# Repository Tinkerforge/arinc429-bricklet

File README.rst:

ARINC429 Bricklet
=================

**This Bricklet is currently in development.**

This repository contains the firmware source code and the hardware design
files. The documentation generator configs can be found at
https://github.com/Tinkerforge/generators

Repository Content
------------------

software/:
 * examples/: Examples for all supported languages
 * build/: Compiled files
 * src/: Source code of firmware
 * Makefile: Makefile to build project

hardware/:
 * Contains KiCad project files and additionally schematics as PDF

datasheets/:
 * Contains datasheets for sensors and complex ICs that are used

Hardware
--------

The hardware is designed with the open source EDA Suite KiCad
(http://www.kicad.org). Before you are able to open the files,
you have to install the Tinkerforge kicad-libraries
(https://github.com/Tinkerforge/kicad-libraries). You can either clone
them directly in hardware/ or clone them in a separate folder and
symlink them into hardware/
(ln -s kicad_path/kicad-libraries project_path/hardware). After that you
can open the .pro file in hardware/ with KiCad and from there view and
modify the schematics and the PCB layout.

Software
--------

If you want to do your own Brick/Bricklet firmware development we highly
recommend that you use our build environment setup script and read the
tutorial (https://www.tinkerforge.com/en/doc/Tutorials/Tutorial_Build_Environment/Tutorial.html).

To compile the C code we recommend you to install the newest GNU Arm Embedded
Toolchain (https://launchpad.net/gcc-arm-embedded/+download).
You also need to install bricklib2 (https://github.com/Tinkerforge/bricklib2).

You can either clone it directly in software/src/ or clone it in a
separate folder and symlink it into software/src/
(ln -s bricklib_path/bricklib2 project_path/software/src/). Finally make sure to
have CMake installed (http://www.cmake.org/cmake/resources/software.html).

After that you can build the firmware by invoking make in software/.
The firmware (.zbin) can then be found in software/build/ and uploaded
with brickv (click button "Flashing" on start screen).

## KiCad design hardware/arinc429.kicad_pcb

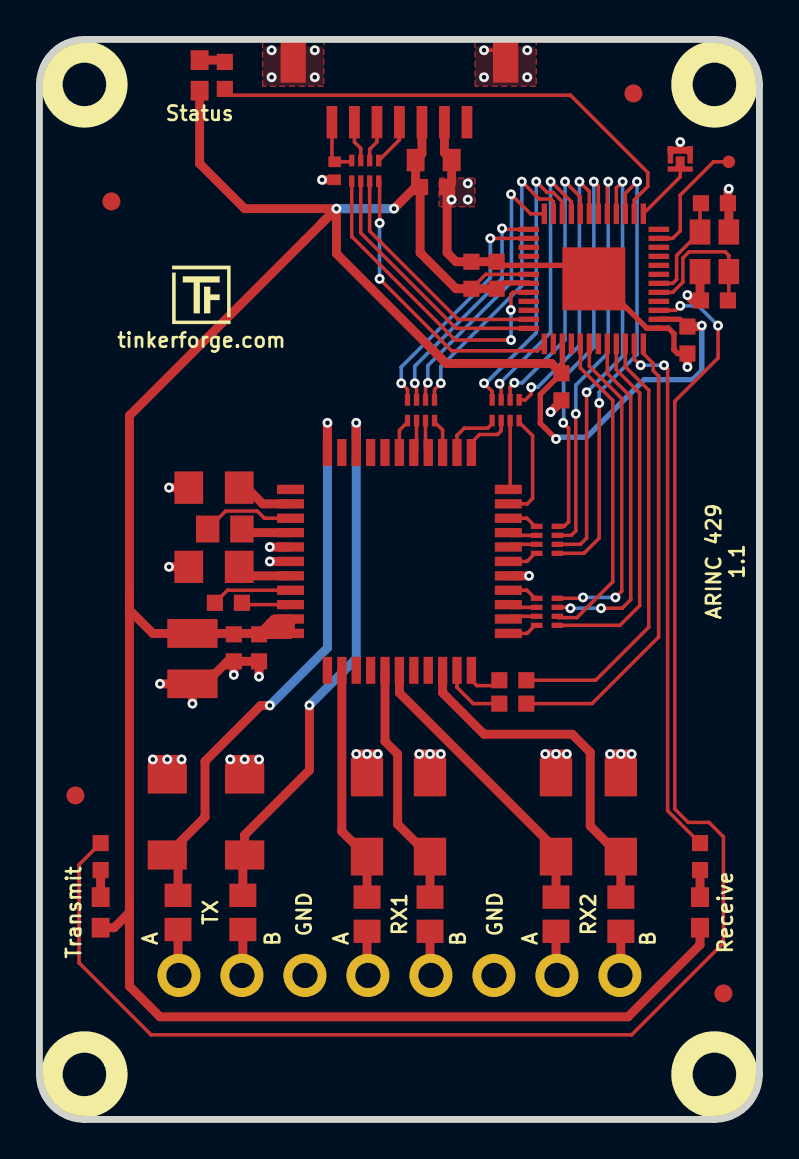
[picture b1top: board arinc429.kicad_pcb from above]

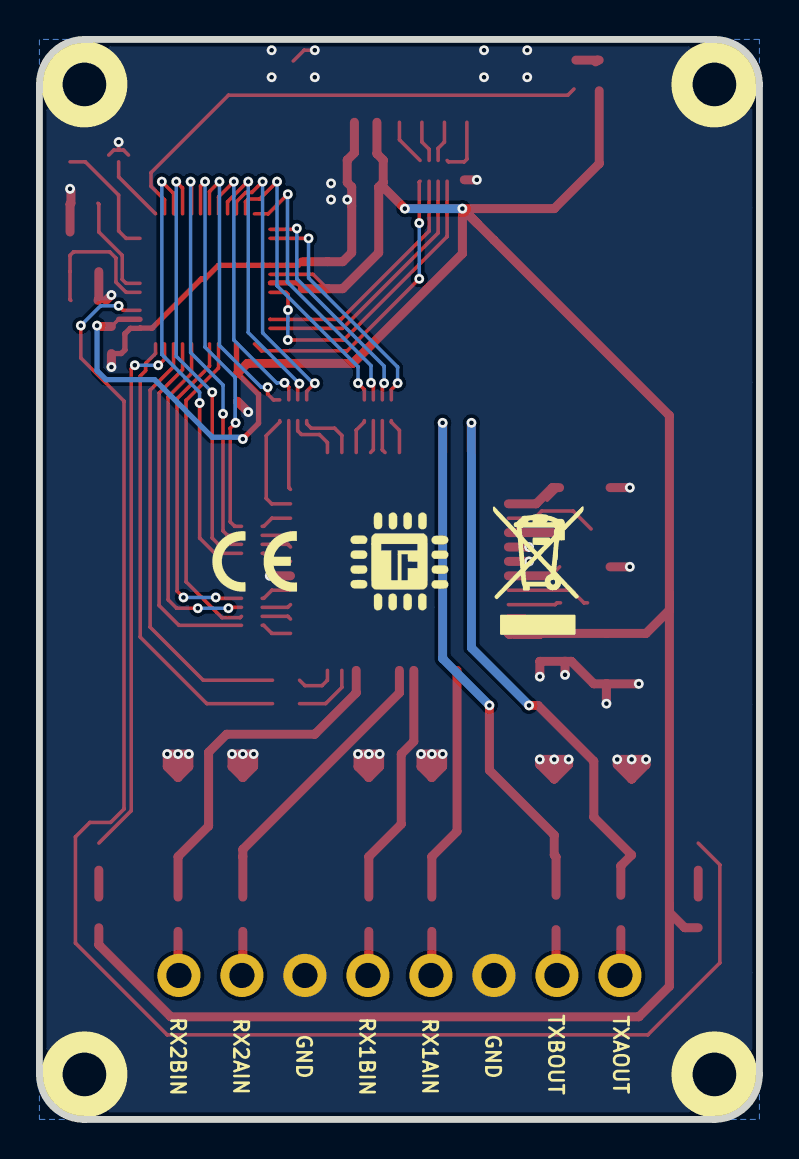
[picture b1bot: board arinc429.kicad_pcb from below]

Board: 2 copper layers, 40.0 x 60.0 mm, 58 parts (2 on the bottom side), 74 nets.

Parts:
C1: 10uF; C0805
C2: 1uF; C0603F
C3, C4, C5, C12: 100nF; C0603F
C6: 220nF; C0603F
C7: 220pF; C0402F
C8, C9: 10pF; C0603F
C10: 47uF; 3528-21
C11: 10nF; C0603F
C13, C15: 47uF/10V; C1206E
C14: 2,2uF/16V; 0805E
C16: 470nF/16V; 0603F
D1, D2: SMBJ-6.5CA; SMB
D3, D8, D9: blue; D0603E
D4, D5, D6, D7: SMAJ-6.5CA; DO-214AC
Fiducial_Mark: VAL**; Fiducial_Mark
Fiducial_Mark#2, Fiducial_Mark#3, Fiducial_Mark#4: VAL**; Fiducial_Mark
P1: CON-SENSOR2
P2: BOOT; SolderJumper
P3: DEBUG; DEBUG_PAD
P4: IND 8Pol; OQ_8P
R1, R10, R11: 1k; R0603F
R2, R3: 100; R0603F
R4, R5, R6, R7: 40,2k; R0805E
R8, R9: 31,6; R0805E
RP1: 82; 4X0402
RP2, RP3, RP4, RP5: 100; 4X0402
U1: XMC1404; QFN48-EP2
U2, U3, U4, U5: DRILL; DRILL_NP
U6: HI-3593PQIF; PQFP-44_10x10mm
VAL: WEEE_7mm
VAL#2: CE_5mm
X1: 16MHz; CRYSTAL_3225

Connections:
CLOCK: R3.2, U1.34
GND: C1.1, C2.1, C3.2, C4.2, C5.2, C6.2, C7.2, C8.2, C9.2, C10.2, C11.1, C12.1, C13.2, C15.2, D1.2, D2.2, D4.2, D5.2, D6.2, D7.2, P1.2, P1.EP, P2.1, P4.3, P4.6, U1.17, U1.37, U1.EP, U6.16, U6.38, U6.39, X1.3
M-CLK: RP5.3, U1.32
M-CS: RP5.1, U1.33
M-MISO: RP5.4, U1.30
M-MOSI: RP5.2, U1.29
MB1-1: RP2.1, U1.3
MB1-2: RP2.2, U1.4
MB1-3: RP2.3, U1.5
MB2-1: RP2.4, U1.6
MB2-2: RP3.1, U1.7
MB2-3: RP3.2, U1.8
unnamed: C7.1, P1.7, RP1.4
unnamed: C8.1, U1.41, X1.2
unnamed: C9.1, U1.42, X1.1
unnamed: C13.1, U6.35
unnamed: C14.1, U6.36
unnamed: C14.2, U6.37
unnamed: C15.1, U6.40
unnamed: C16.1, U6.41
unnamed: C16.2, U6.42
unnamed: D1.1, R9.2, U6.33
unnamed: D2.1, R8.2, U6.31
unnamed: D3.2, R11.2
unnamed: D4.1, R7.2, U6.2
unnamed: D5.1, R6.2, U6.5
unnamed: D6.1, R5.2, U6.6
unnamed: D7.1, R4.2, U6.9
unnamed: D8.2, R1.2
unnamed: D9.2, R10.2
unnamed: P1.4, RP1.1
unnamed: P1.5, RP1.2
unnamed: P1.6, RP1.3
unnamed: P2.2, U1.1
unnamed: P3.1, U1.47
unnamed: P4.1, R9.1
unnamed: P4.2, R8.1
unnamed: P4.4, R7.1
unnamed: P4.5, R6.1
unnamed: P4.7, R5.1
unnamed: P4.8, R4.1
unnamed: R2.1, U6.10
unnamed: R3.1, U6.11
unnamed: RP2.5, U6.20
unnamed: RP2.6, U6.19
unnamed: RP2.7, U6.18
unnamed: RP2.8, U6.17
unnamed: RP3.5, U6.24
unnamed: RP3.6, U6.23
unnamed: RP3.7, U6.22
unnamed: RP3.8, U6.21
unnamed: RP4.5, U6.28
unnamed: RP4.6, U6.27
unnamed: RP4.7, U6.26
unnamed: RP4.8, U6.25
unnamed: RP5.5, U6.15
unnamed: RP5.6, U6.14
unnamed: RP5.7, U6.13
unnamed: RP5.8, U6.12
R1FLAG: RP4.2, U1.12
R1INT: RP4.1, U1.11
R2FLAG: RP3.4, U1.10
R2INT: RP3.3, U1.9
RESET: R2.2, U1.36
RX_LED: R10.1, U1.39
S-CLK: RP1.7, U1.23
S-CS: RP1.8, U1.25
S-MISO: RP1.5, U1.20
S-MOSI: RP1.6, U1.24
Status_LED: R11.1, U1.2
TEMPY: RP4.3, U1.13
TFULL: RP4.4, U1.14
TX_LED: R1.1, U1.35
VCC: C1.2, C2.2, C3.1, C4.1, C5.1, C6.1, C10.1, C11.2, C12.2, D3.1, D8.1, D9.1, P1.3, U1.18, U1.19, U1.27, U1.38, U6.43, U6.44

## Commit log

2020-06-26 first schematic
2020-06-26 first pcb
2020-06-29 pcb design
2020-06-29 pcb prototyp
2020-06-29 ready for prototype
2020-06-29 fixed copper floodfill
2020-06-30 add description text on top side
2020-06-30 remove double text
2020-07-23 Add initial firmware stub implementation
2020-07-23 changed spi pinout
2020-07-23 Add HI3593 pin and hardware unit defines
2020-07-23 Initialize pins and spi, add register read/write test
2020-07-24 Put bootloader and communication tick in coop task
    With this we can call other coop tasks from within a getter/setter
2020-07-24 Active spi fifo coop mutex
    This is necessary since we now can use SPI from the hi3593 tick
    as well as from a getter/setter
2020-07-24 Fix typo
2020-07-24 Use 32 words per spi fifo
2020-07-24 Add opcode length table
2020-07-24 Remove test code, make input pins and register read/write functions available
2020-07-24 Implement simple debug API
    Note: We du the SPI read/write directly in the communication
    setter/getter call here and the setter/getter is blocked as long
    as the communication takes.
    This makes sense for the debug code, but later on the firmware will
    have to do the more high-level logic in the hi3593 tick.
2020-07-24 Add loopback test
2020-07-24 Add simple RX/TX led logic
    For now we blink rx when we read registers and tx when we write registers
2020-07-24 Sanity check write register value length
2020-08-26 Add test for two ARINC429 Bricklets
2020-08-26 Decrease coop task stack and SPITFP receive buffer size
2020-08-26 Add data structure for ARINC429 state machine
    This is currently just for memory/stack size testing. We can
    still optimize it so the packing is not necessary and access
    of the data is faster.
2020-08-31 Add auto-generated API stubs
2020-08-31 Add getter/setter channel sanity-check for API functions
2020-08-31 Add implementation for set/get channel configuration
    * Use memory-efficient "V3-datastructure" and increase coop task size again
    * Move common configurations to tx/rx channel
    * Add first high-level function test
2020-09-01 Add initialization comments
2020-09-01 Implement get_capabilities API function
2020-09-01 Clear FIFO before configuration and set active afterwards
2020-09-01 Remove redundent A429 prefix
2020-09-01 Remove unused datastructure alternative
2020-09-01 Add implementation for set/get_channel_mode
2020-09-01 Remove debug
2020-09-01 Add get/set/clear prio label implementation
2020-09-01 Update test script
2020-09-01 Add stub task functions
2020-10-06 Add API implementation and business logic
2020-10-06 Remove hi3593 coop task
    This task was only used during the initialization, we move the
    initialization in the arinc429 task instead. This saves 2kB of RAM.
2020-10-06 Comment in communication_callback_init/tick
    Used for handle_callbacks function
2020-10-06 Because all callbacks are implemented in one function wenn need CALLBACK_NUM = 1
2020-10-06 Update bindings
2020-10-09 Match naming between generator and firmware
2020-10-28 Improve ARINC429 implementation and API
2020-10-28 Add fw and speed test, update bindings
2020-10-28 Fix LEDs
2020-10-28 Improve naming and documentation
2020-10-28 Improve test, update bindings
2021-01-25 Improve naming and small fixes
2021-01-25 Add more tests
2021-02-24 edited F.Paste layer
2021-03-04 Use channel->tail instead of next_tail
2021-03-04 Fix negative number in BNR format
2021-04-22 Implement API changes
2021-05-26 added specific partnumber HI-3593PQIF
2021-05-27 Add channel to scheduler callback
2021-10-25 Update KiCad link
    https://www.kicad.org/blog/2021/10/Avoid-links-to-former-kicad-domain/
2022-07-06 Add license files.
2025-10-04 Fix compatibility with new Docker build image (GCC 14.2.1)

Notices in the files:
hardware/arinc429.kicad_pcb:
Licensed under CERN OHL v.1.1
Copyright (©) 2020, T.Schneidermann
Copyright Tinkerforge GmbH 2020.
This documentation describes Open Hardware and is licensed under the
CERN OHL v. 1.1.
